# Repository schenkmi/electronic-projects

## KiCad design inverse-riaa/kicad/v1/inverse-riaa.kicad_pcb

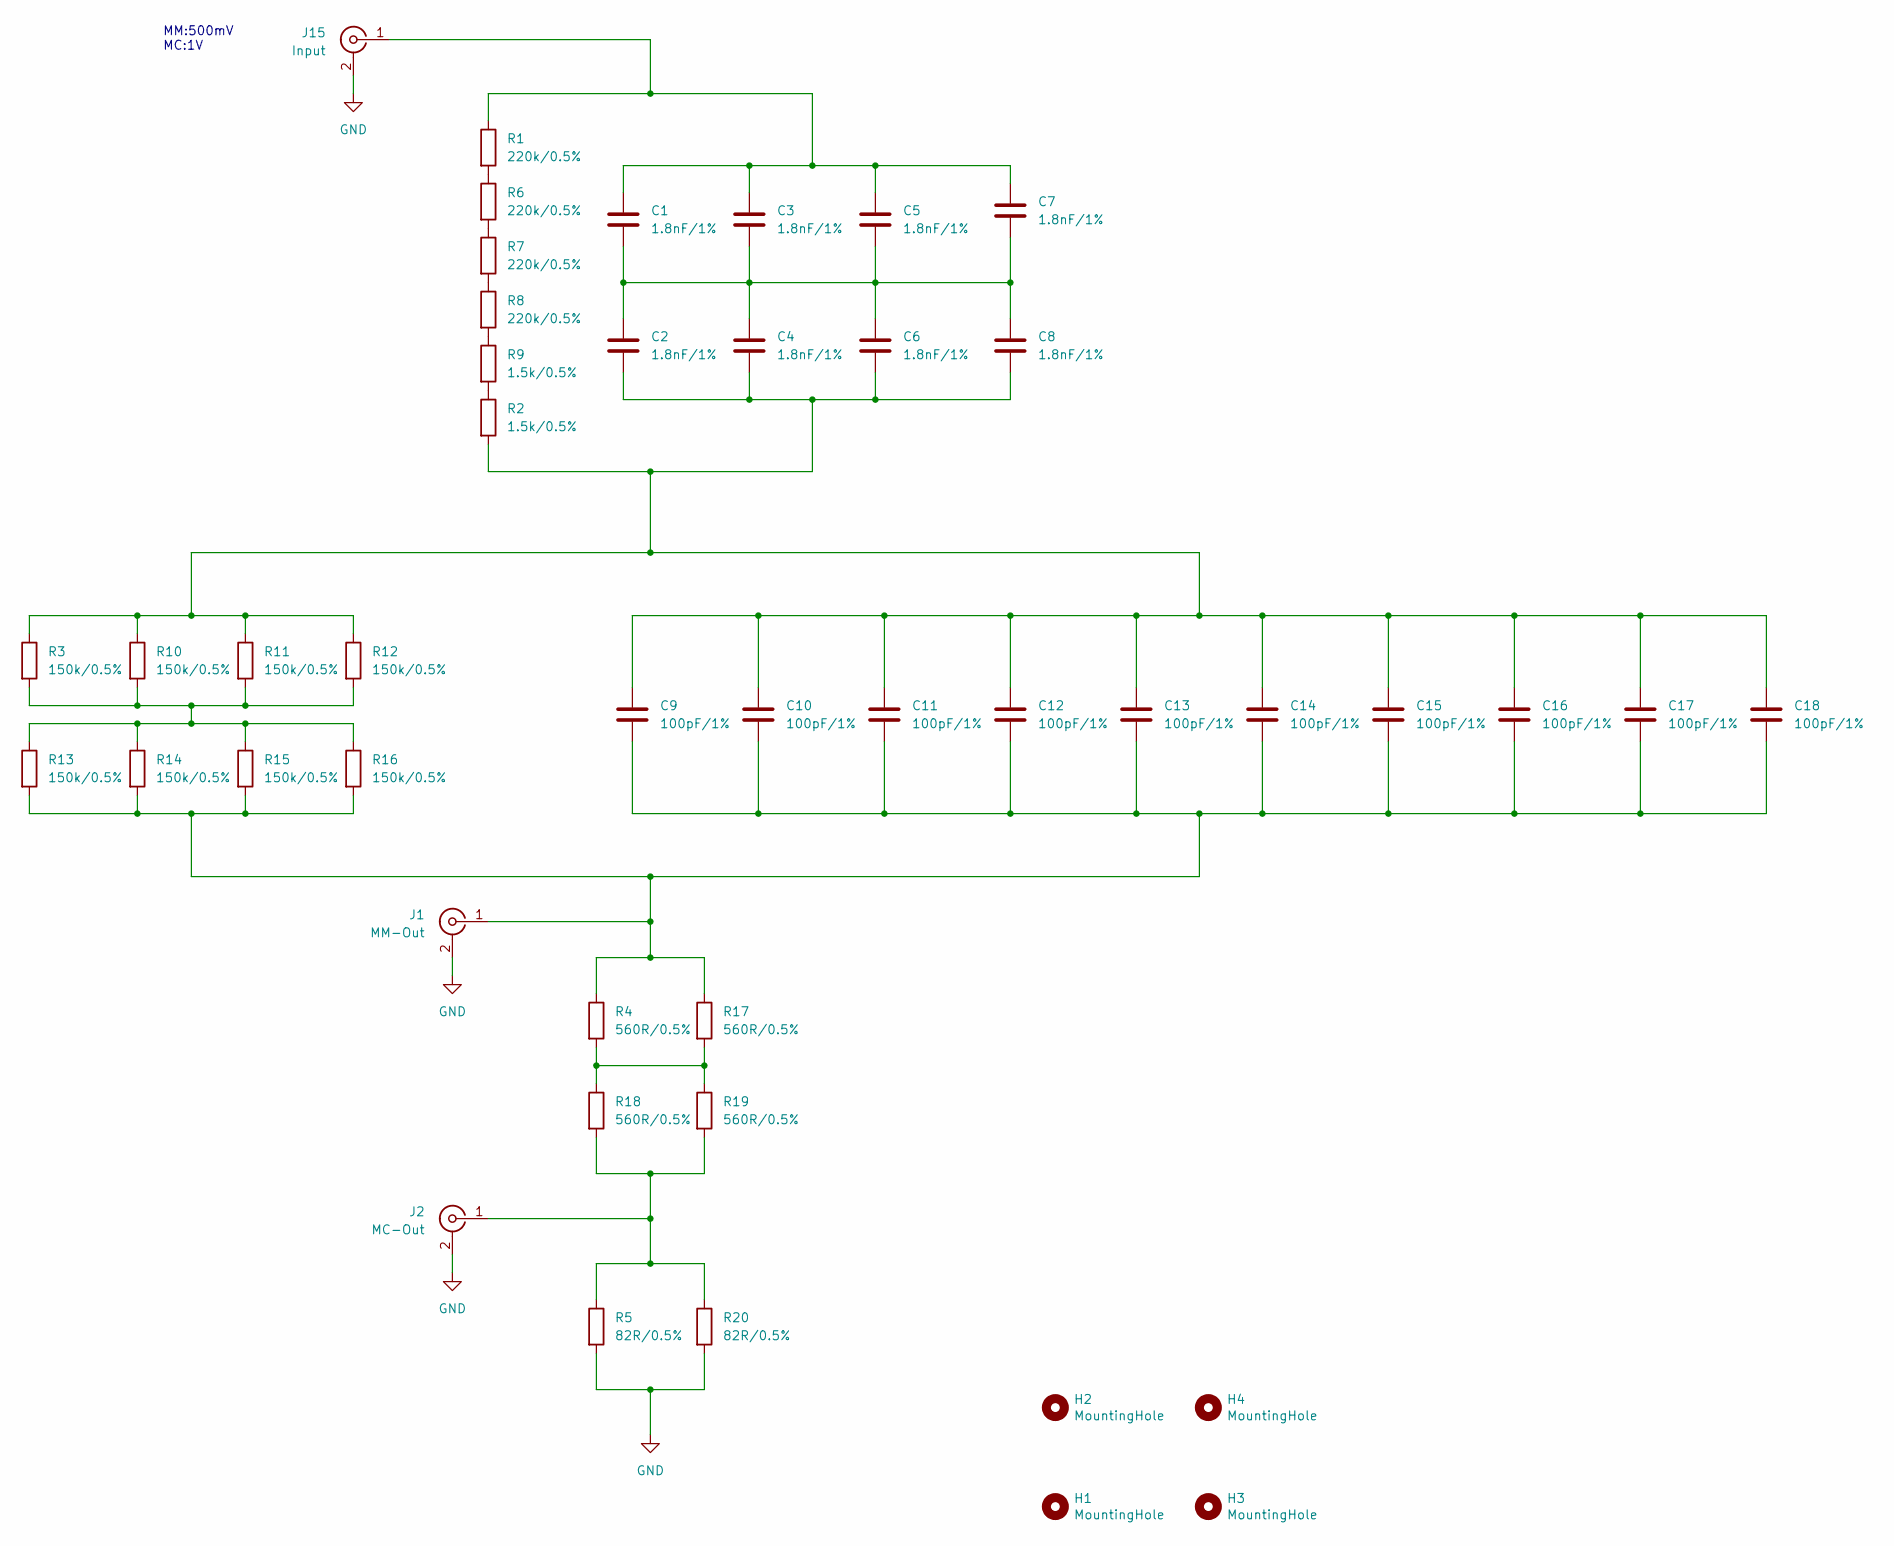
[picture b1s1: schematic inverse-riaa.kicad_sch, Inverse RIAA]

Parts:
C1, C2, C3, C4, C5, C6, C7, C8: 1.8nF/1%; C_0805_2012Metric_Pad1.18x1.45mm_HandSolder
C9, C10, C11, C12, C13, C14, C15, C16, C17, C18: 100pF/1%; C_0805_2012Metric_Pad1.18x1.45mm_HandSolder
H1, H2, H3, H4: MountingHole; MountingHole_3.2mm_M3_Pad_Via
J1: MM-Out; RCA-Phono_CUI-Devices_RCJ-02X_Vertical
J2: MC-Out; RCA-Phono_CUI-Devices_RCJ-02X_Vertical
J15: Input; RCA-Phono_CUI-Devices_RCJ-02X_Vertical
R1, R6, R7, R8: 220k/0.5%; R_0805_2012Metric_Pad1.20x1.40mm_HandSolder
R2, R9: 1.5k/0.5%; R_0805_2012Metric_Pad1.20x1.40mm_HandSolder
R3, R10, R11, R12, R13, R14, R15, R16: 150k/0.5%; R_0805_2012Metric_Pad1.20x1.40mm_HandSolder
R4, R17, R18, R19: 560R/0.5%; R_0805_2012Metric_Pad1.20x1.40mm_HandSolder
R5, R20: 82R/0.5%; R_0805_2012Metric_Pad1.20x1.40mm_HandSolder

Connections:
GND: J1.2 (Ext), J2.2 (Ext), J15.2 (Ext), R5.2, R20.2
unnamed: C1.2, C2.1, C3.2, C4.1, C5.2, C6.1, C7.2, C8.1
unnamed: C2.2, C4.2, C6.2, C8.2, C9.1, C10.1, C11.1, C12.1, C13.1, C14.1, C15.1, C16.1, C17.1, C18.1, R2.2, R3.1, R10.1, R11.1, R12.1
unnamed: C9.2, C10.2, C11.2, C12.2, C13.2, C14.2, C15.2, C16.2, C17.2, C18.2, J1.1 (In), R4.1, R13.2, R14.2, R15.2, R16.2, R17.1
unnamed: J2.1 (In), R5.1, R18.2, R19.2, R20.1
unnamed: C1.1, C3.1, C5.1, C7.1, J15.1 (In), R1.1
unnamed: R1.2, R6.1
unnamed: R2.1, R9.2
unnamed: R6.2, R7.1
unnamed: R7.2, R8.1
unnamed: R8.2, R9.1
unnamed: R3.2, R10.2, R11.2, R12.2, R13.1, R14.1, R15.1, R16.1
unnamed: R4.2, R17.2, R18.1, R19.1

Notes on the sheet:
MM:500mV MC:1V

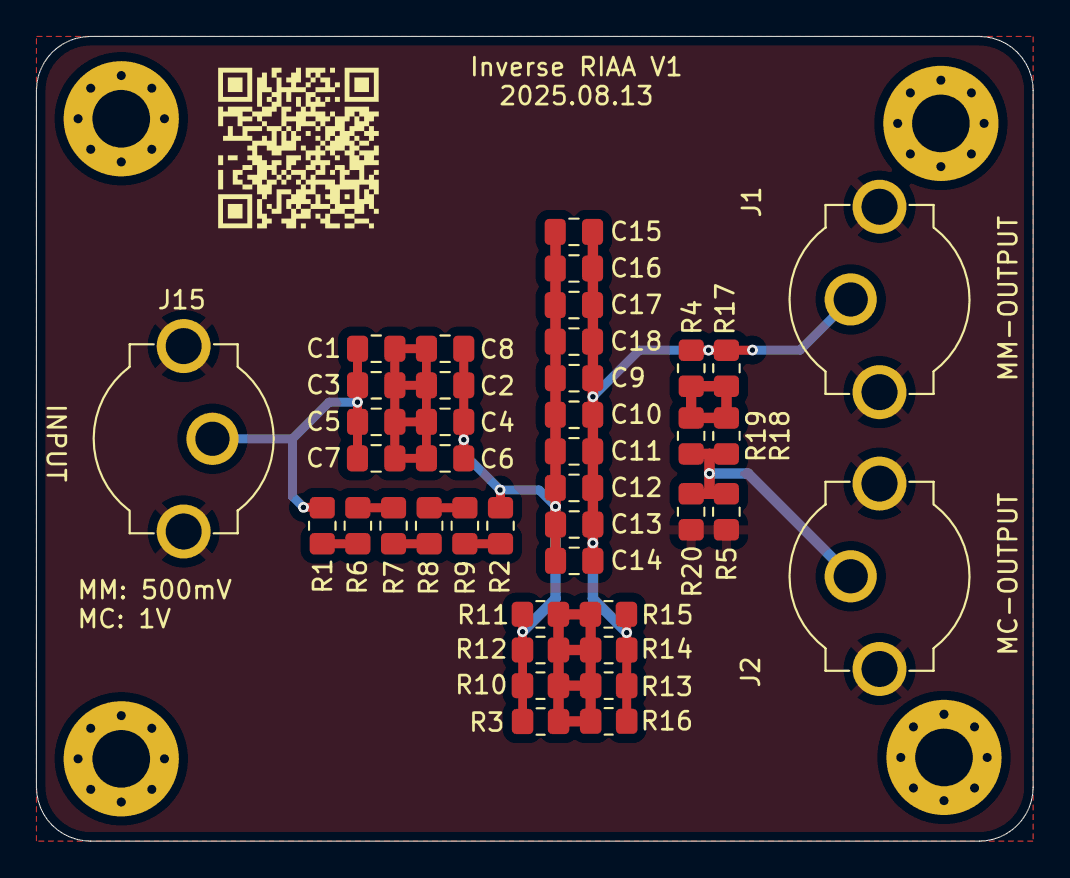
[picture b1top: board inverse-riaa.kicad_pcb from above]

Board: 2 copper layers, 55.4 x 44.7 mm, 45 parts (0 on the bottom side), 13 nets.

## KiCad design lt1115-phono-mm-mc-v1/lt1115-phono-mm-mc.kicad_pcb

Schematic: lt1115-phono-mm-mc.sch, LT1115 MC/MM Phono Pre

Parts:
C1: C; C_0805_2012Metric_Pad1.18x1.45mm_HandSolder
C2: 4.7uF; C_Rect_L7.2mm_W7.2mm_P5.00mm_FKS2_FKP2_MKS2_MKP2
C3: 2200uF/16V; CP_Radial_D10.0mm_P5.00mm
C4, C7, C11, C14: 220uF/25V; CP_Radial_D8.0mm_P3.50mm
C5, C6, C12, C13: 1uF; C_1210_3225Metric_Pad1.33x2.70mm_HandSolder
C8: 330pF; C_0805_2012Metric_Pad1.18x1.45mm_HandSolder
C9, C15: 3.9nF; C_1206_3216Metric_Pad1.33x1.80mm_HandSolder
C10: 15nF; C_1210_3225Metric_Pad1.33x2.70mm_HandSolder
C16, C19: 1uF; C_Rect_L7.2mm_W3.5mm_P5.00mm_FKS2_FKP2_MKS2_MKP2
C17, C18: 100nF; C_0805_2012Metric_Pad1.18x1.45mm_HandSolder
H1, H2, H3, H4: MountingHole; MountingHole_3.2mm_M3
HS1: Heatsink; Heatsink_Fischer_SK104-STC-STIC_35x13mm_2xDrill2.5mm
J1: INR; Pin_D1.0mm_L10.0mm
J2: INR_GND; Pin_D1.0mm_L10.0mm
J3: +15V; Pin_D1.0mm_L10.0mm
J4: GND; Pin_D1.0mm_L10.0mm
J5: -15V; Pin_D1.0mm_L10.0mm
J6: OUTR; Pin_D1.0mm_L10.0mm
J7: OUTR_GND; Pin_D1.0mm_L10.0mm
R1, R11: 100R; R_0805_2012Metric_Pad1.20x1.40mm_HandSolder
R2: 22.6R; R_0805_2012Metric_Pad1.20x1.40mm_HandSolder
R3: 210R; R_0805_2012Metric_Pad1.20x1.40mm_HandSolder
R4: 0R; R_0805_2012Metric_Pad1.20x1.40mm_HandSolder
R5: 449R; R_0805_2012Metric_Pad1.20x1.40mm_HandSolder
R6: 33.2k; R_0805_2012Metric_Pad1.20x1.40mm_HandSolder
R7: 17.8k; R_0805_2012Metric_Pad1.20x1.40mm_HandSolder
R8: 82.5k; R_0805_2012Metric_Pad1.20x1.40mm_HandSolder
R9: 33.2R; R_0805_2012Metric_Pad1.20x1.40mm_HandSolder
R10: 210k; R_0805_2012Metric_Pad1.20x1.40mm_HandSolder
R12: 49.9R; R_0805_2012Metric_Pad1.20x1.40mm_HandSolder
R13: 562R; R_0805_2012Metric_Pad1.20x1.40mm_HandSolder
R14: 25k; R_0805_2012Metric_Pad1.20x1.40mm_HandSolder
R15, R16: 100k; R_0805_2012Metric_Pad1.20x1.40mm_HandSolder
U1: LT1115; DIP-8_W7.62mm
U2: LM334M; SOIC-8_3.9x4.9mm_P1.27mm
U3: LT1010; TO-220-5_P3.4x3.7mm_StaggerOdd_Lead3.8mm_Vertical
U4: OPA188xxDBV; TSOT-23-5

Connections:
+15V: C4.1, C5.1, C11.1, C12.1, C17.1, J3.1, R12.1, U1.7 (V+), U3.2 (V+), U4.5 (V+)
-15V: C6.2, C7.2, C13.2, C14.2, C18.2, J5.1, R9.2, U1.4 (V-), U2.2, U2.3, U2.6, U2.7, U3.3 (V-), U4.2 (V-)
GND: C1.2, C2.1, C3.2, C4.2, C5.2, C6.1, C7.1, C11.2, C12.2, C13.1, C14.1, C15.2, C17.2, C18.1, C19.1, J2.1, J4.1, J7.1, R1.2, R6.1, R14.2, R15.2
unnamed: C1.1, J1.1, R1.1, U1.3 (+)
unnamed: C2.2, C3.1, R3.2, R4.2, R8.2
unnamed: C8.2, C9.2, R5.1, R7.2
unnamed: C8.1, C9.1, C10.2, R7.1, R10.2
unnamed: C15.1, J6.1, R13.1, R14.1
unnamed: C16.2, R16.1, U4.4 (-)
unnamed: C19.2, R15.1, U4.3 (+)
unnamed: R2.1, R5.2, U1.2 (-)
unnamed: R2.2, R3.1, R4.1
unnamed: R6.2, U1.1 (TRIM)
unnamed: R9.1, U2.1
unnamed: R11.1, U3.1 (IN)
unnamed: R11.2, U1.6, U2.4
unnamed: R12.2, U3.4 (BIAS)
SERVO_INR: C10.1, R8.1, R10.1, R13.2, R16.2, U3.5 (OUT)
SERVO_OUTR: C16.1, U1.8 (TRIM), U4.1

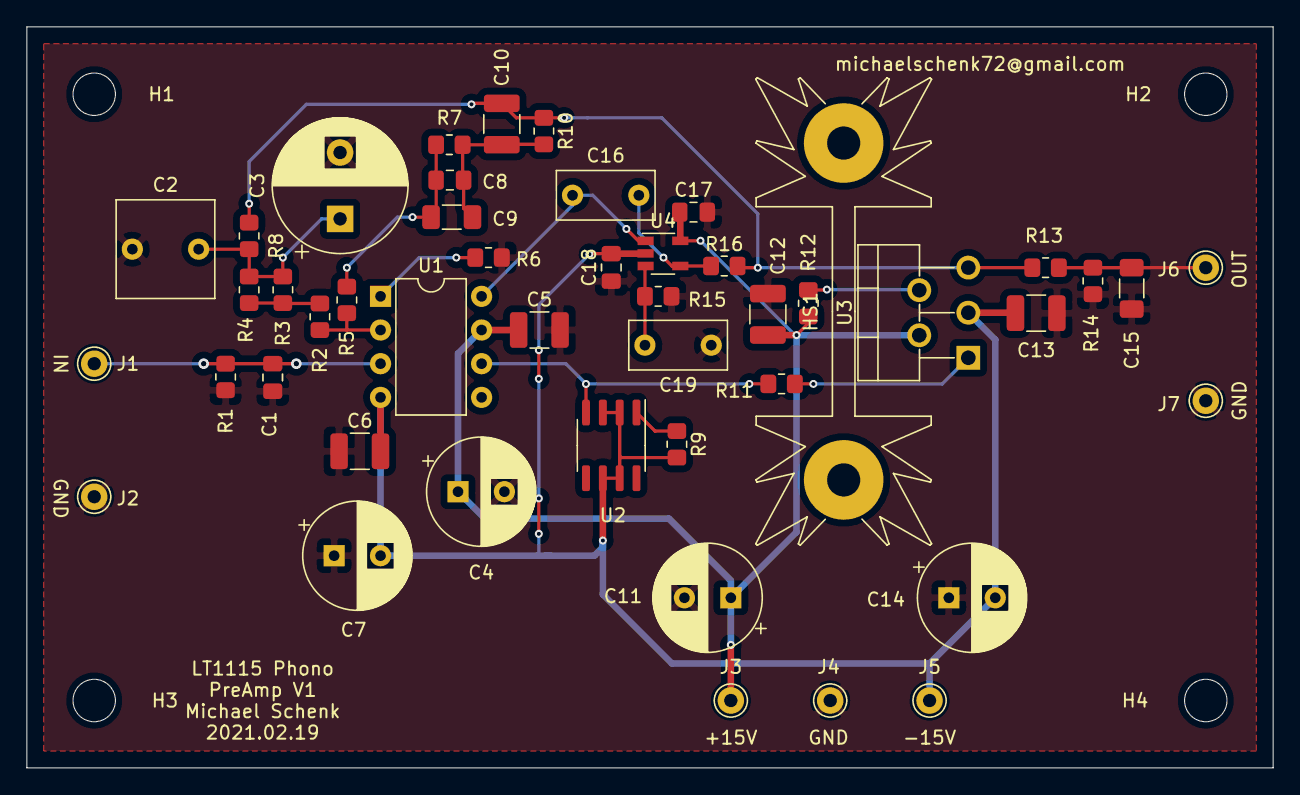
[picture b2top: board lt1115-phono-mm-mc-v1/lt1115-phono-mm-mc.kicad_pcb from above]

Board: 2 copper layers, 94.0 x 55.9 mm, 51 parts (0 on the bottom side), 19 nets.

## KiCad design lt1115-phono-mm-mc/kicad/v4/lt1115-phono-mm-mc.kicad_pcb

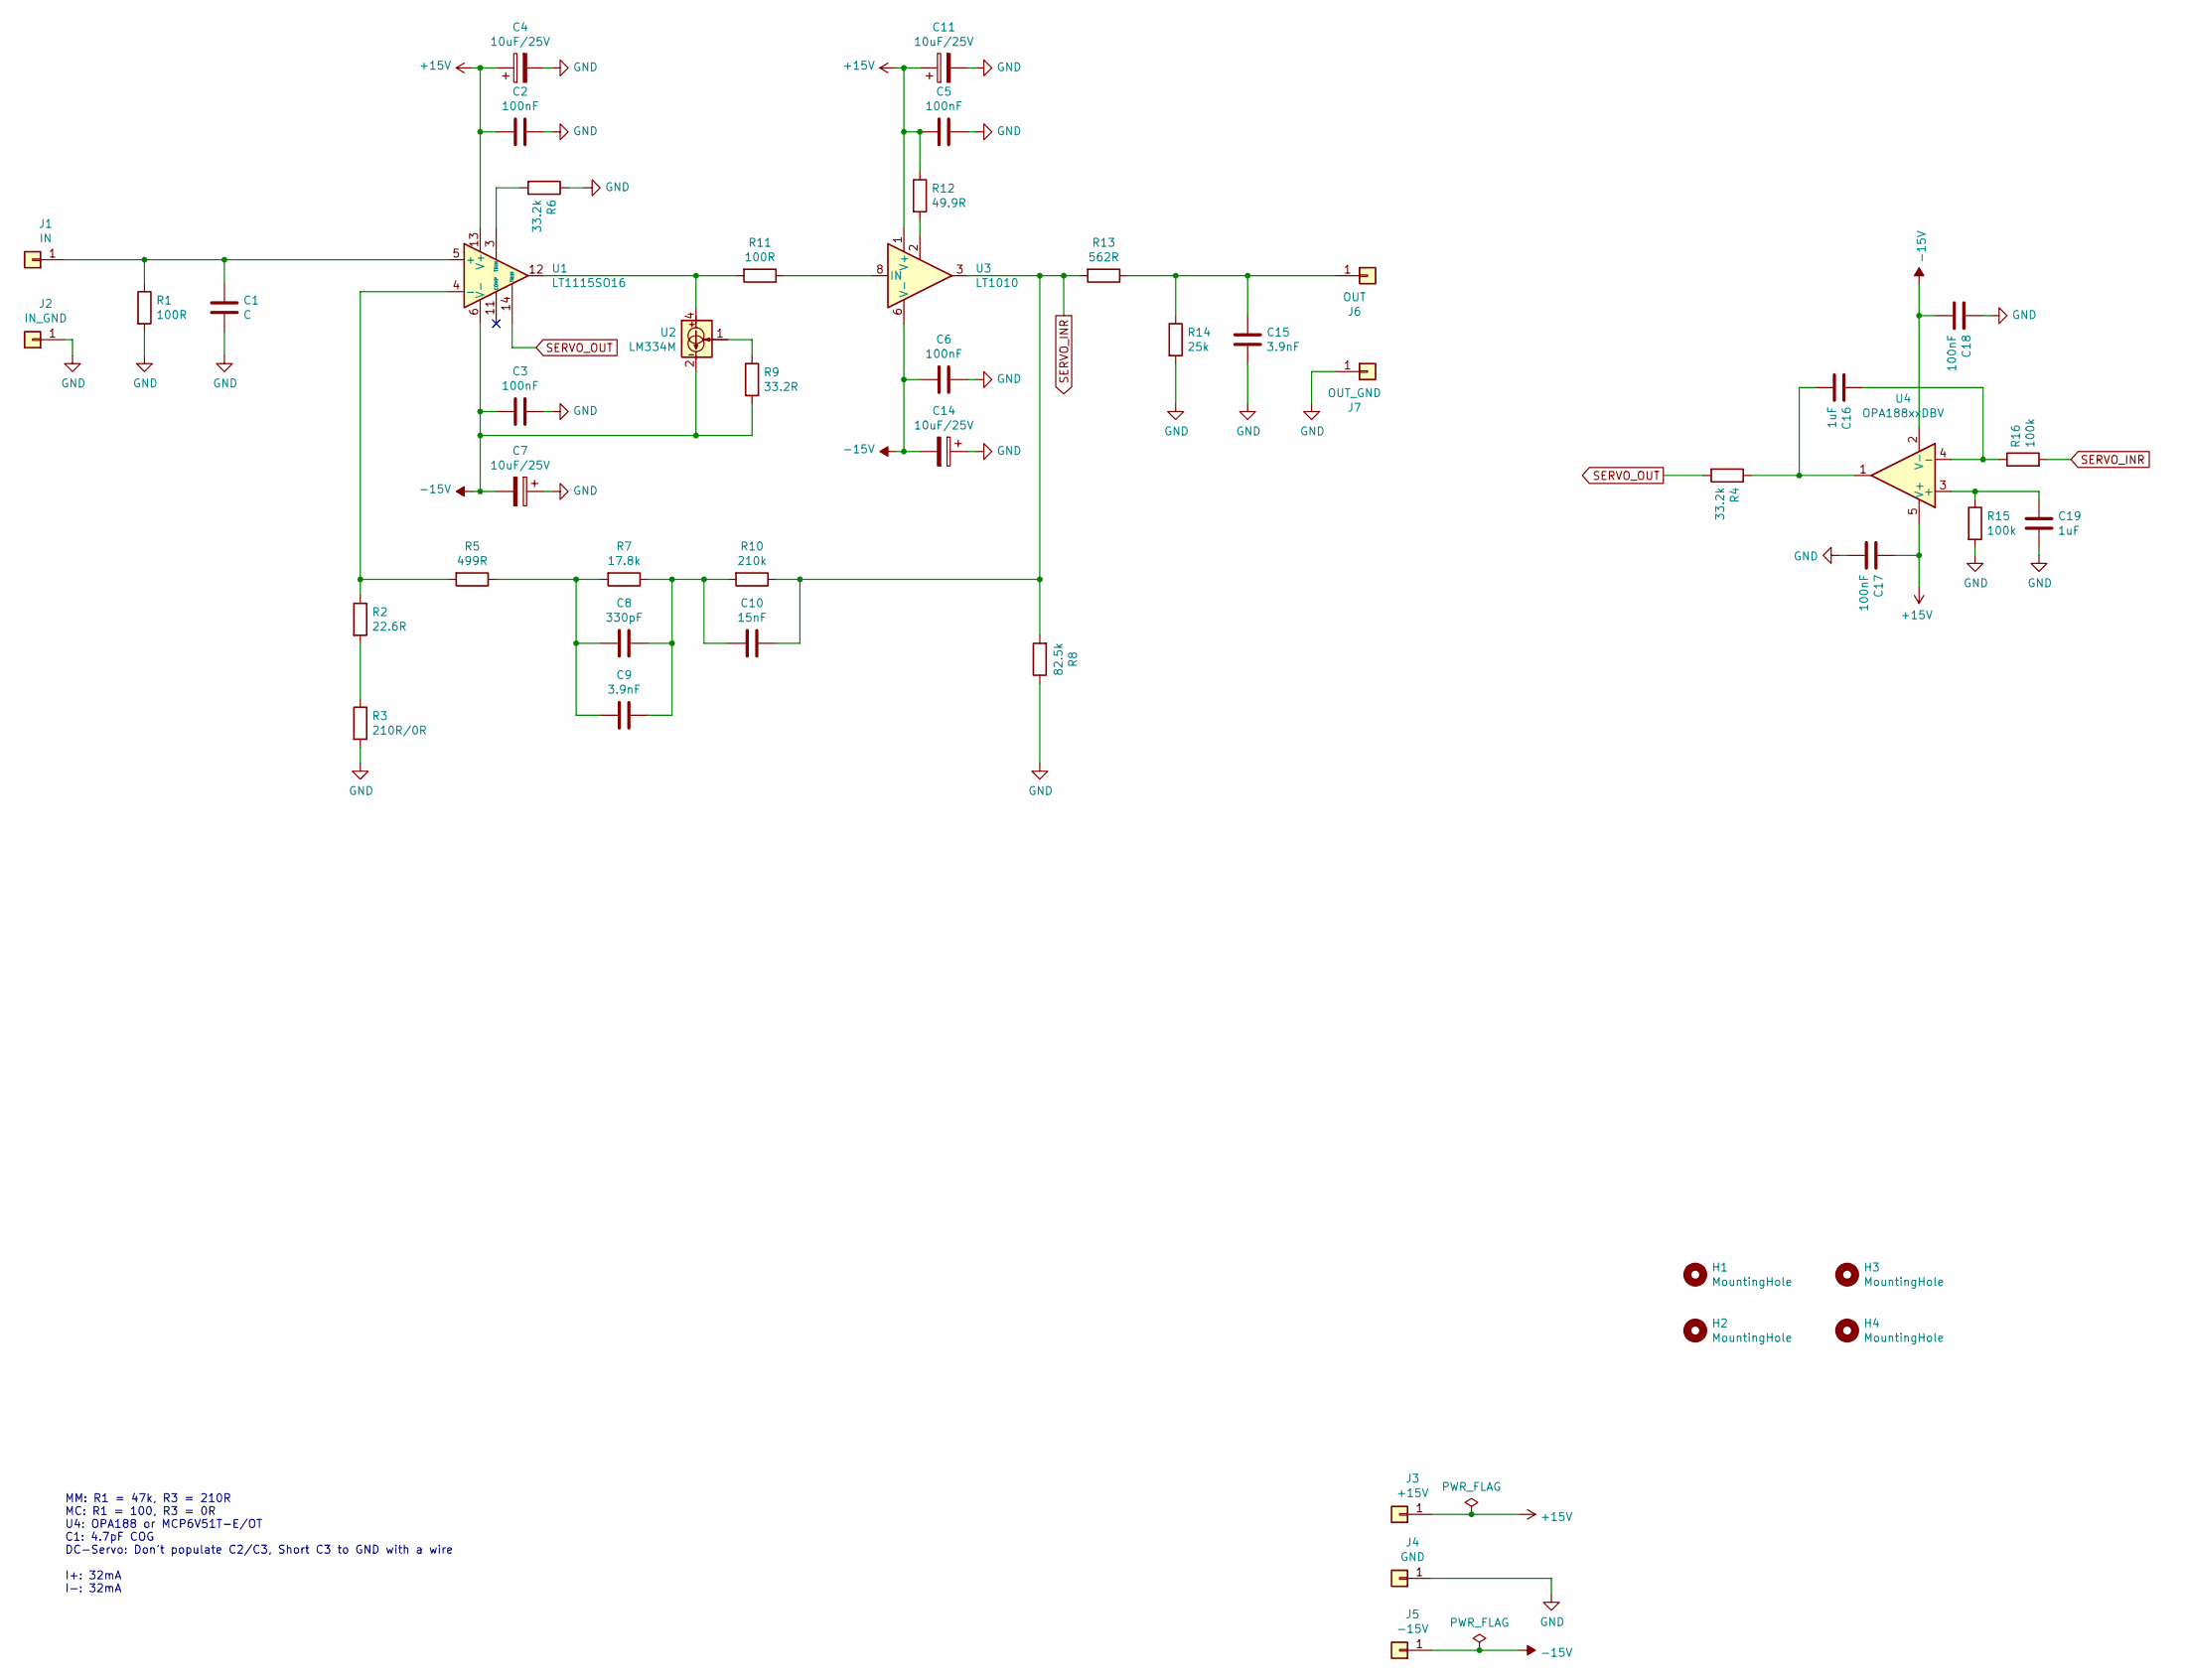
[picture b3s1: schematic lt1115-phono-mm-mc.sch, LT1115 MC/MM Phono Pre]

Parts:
C1: C; C_0805_2012Metric_Pad1.18x1.45mm_HandSolder
C2, C3, C5, C6: 100nF; C_1210_3225Metric_Pad1.33x2.70mm_HandSolder
C4, C7, C11, C14: 10uF/25V; CP_Elec_6.3x5.8
C8: 330pF; C_0805_2012Metric_Pad1.18x1.45mm_HandSolder
C9, C15: 3.9nF; C_1206_3216Metric_Pad1.33x1.80mm_HandSolder
C10: 15nF; C_1210_3225Metric_Pad1.33x2.70mm_HandSolder
C16, C19: 1uF; C_1210_3225Metric_Pad1.33x2.70mm_HandSolder
C17, C18: 100nF; C_0805_2012Metric_Pad1.18x1.45mm_HandSolder
H1, H2, H3, H4: MountingHole; MountingHole_3.2mm_M3
J1: IN; Pin_D1.0mm_L10.0mm
J2: IN_GND; Pin_D1.0mm_L10.0mm
J3: +15V; Pin_D1.0mm_L10.0mm
J4: GND; Pin_D1.0mm_L10.0mm
J5: -15V; Pin_D1.0mm_L10.0mm
J6: OUT; Pin_D1.0mm_L10.0mm
J7: OUT_GND; Pin_D1.0mm_L10.0mm
R1, R11: 100R; R_0805_2012Metric_Pad1.20x1.40mm_HandSolder
R2: 22.6R; R_0805_2012Metric_Pad1.20x1.40mm_HandSolder
R3: 210R/0R; R_0805_2012Metric_Pad1.20x1.40mm_HandSolder
R4, R6: 33.2k; R_0805_2012Metric_Pad1.20x1.40mm_HandSolder
R5: 499R; R_0805_2012Metric_Pad1.20x1.40mm_HandSolder
R7: 17.8k; R_0805_2012Metric_Pad1.20x1.40mm_HandSolder
R8: 82.5k; R_0805_2012Metric_Pad1.20x1.40mm_HandSolder
R9: 33.2R; R_0805_2012Metric_Pad1.20x1.40mm_HandSolder
R10: 210k; R_0805_2012Metric_Pad1.20x1.40mm_HandSolder
R12: 49.9R; R_0805_2012Metric_Pad1.20x1.40mm_HandSolder
R13: 562R; R_0805_2012Metric_Pad1.20x1.40mm_HandSolder
R14: 25k; R_0805_2012Metric_Pad1.20x1.40mm_HandSolder
R15, R16: 100k; R_0805_2012Metric_Pad1.20x1.40mm_HandSolder
U1: LT1115SO16; SOIC-16W_7.5x10.3mm_P1.27mm
U2: LM334M; SOIC-8_3.9x4.9mm_P1.27mm
U3: LT1010; DFN-8-1EP_3x3mm_P0.5mm_EP1.66x2.38mm
U4: OPA188xxDBV; TSOT-23-5

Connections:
+15V: C2.2, C4.1, C5.2, C11.1, C17.1, J3.1, R12.1, U1.13 (V+), U3.1 (V+), U4.5 (V+)
-15V: C3.2, C6.2, C7.2, C14.2, C18.2, J5.1, R9.2, U1.6 (V-), U2.2, U2.3, U2.6, U2.7, U3.6 (V-), U4.2 (V-)
GND: C1.2, C2.1, C3.1, C4.2, C5.1, C6.1, C7.1, C11.2, C14.1, C15.2, C17.2, C18.1, C19.1, J2.1, J4.1, J7.1, R1.2, R3.2, R6.1, R8.1, R14.2, R15.2
unnamed: C1.1, J1.1, R1.1, U1.5 (+)
unnamed: C8.2, C9.2, R5.1, R7.2
unnamed: C8.1, C9.1, C10.2, R7.1, R10.2
unnamed: C15.1, J6.1, R13.1, R14.1
unnamed: C16.1, R4.1, U4.1
unnamed: C16.2, R16.1, U4.4 (-)
unnamed: C19.2, R15.1, U4.3 (+)
unnamed: R2.1, R5.2, U1.4 (-)
unnamed: R2.2, R3.1
unnamed: R6.2, U1.3 (TRIM)
unnamed: R9.1, U2.1
unnamed: R11.1, U3.8 (IN)
unnamed: R11.2, U1.12, U2.4
unnamed: R12.2, U3.2
SERVO_INR: C10.1, R8.2, R10.1, R13.2, R16.2, U3.3
SERVO_OUT: R4.2, U1.14 (TRIM)

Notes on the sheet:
MM: R1 = 47k, R3 = 210R MC: R1 = 100, R3 = 0R U4: OPA188 or MCP6V51T-E/OT C1: 4.7pF COG DC-Servo: Don’t populate C2/C3, Short C3 to GND with a wire I+: 32mA I-: 32mA

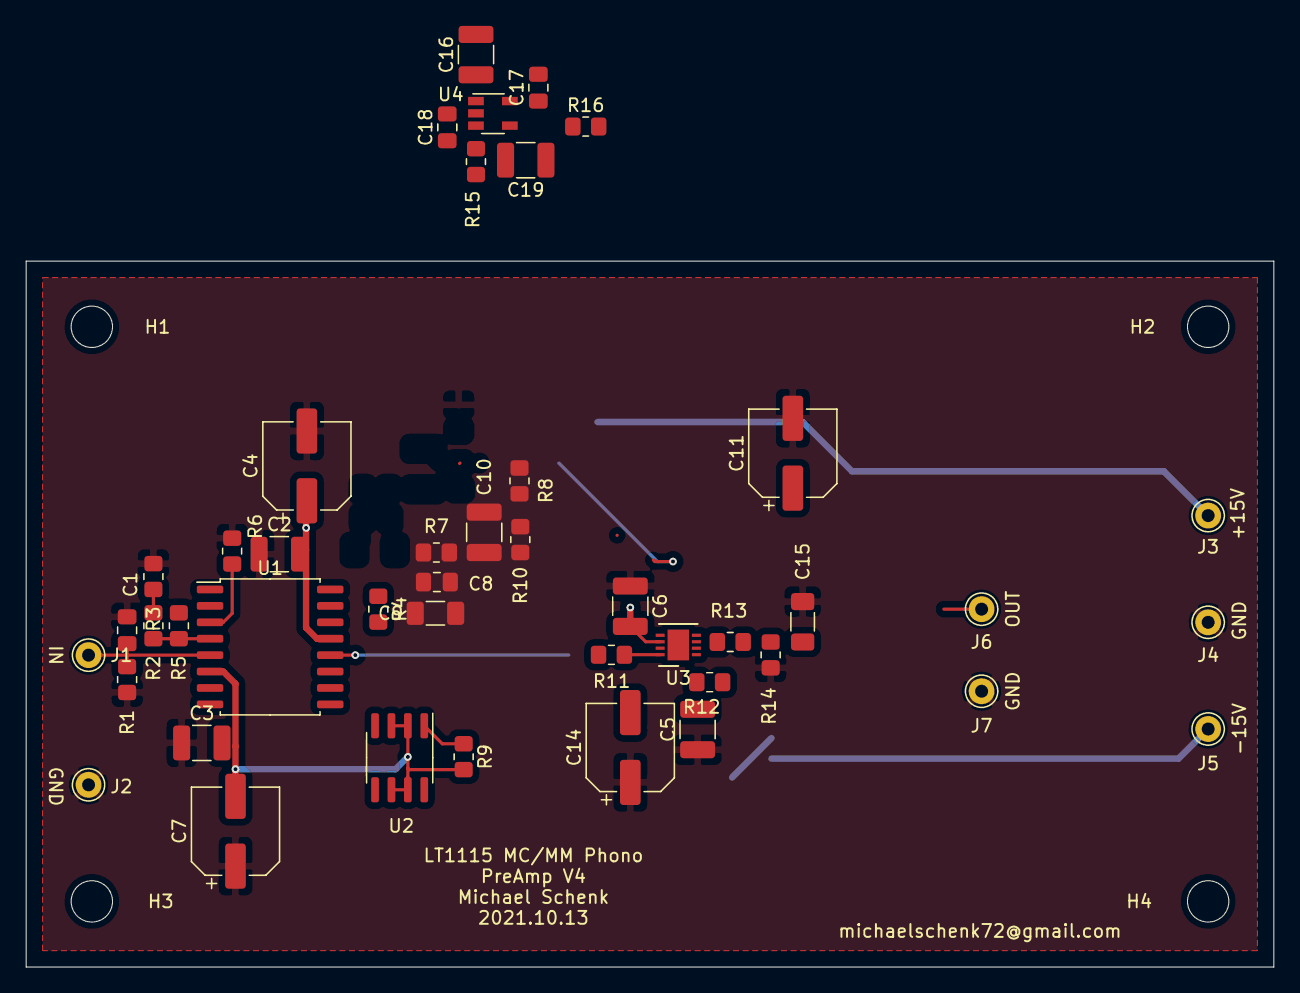
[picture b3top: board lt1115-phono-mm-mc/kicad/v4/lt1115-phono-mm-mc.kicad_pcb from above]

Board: 2 copper layers, 96.5 x 54.6 mm, 48 parts (0 on the bottom side), 19 nets.

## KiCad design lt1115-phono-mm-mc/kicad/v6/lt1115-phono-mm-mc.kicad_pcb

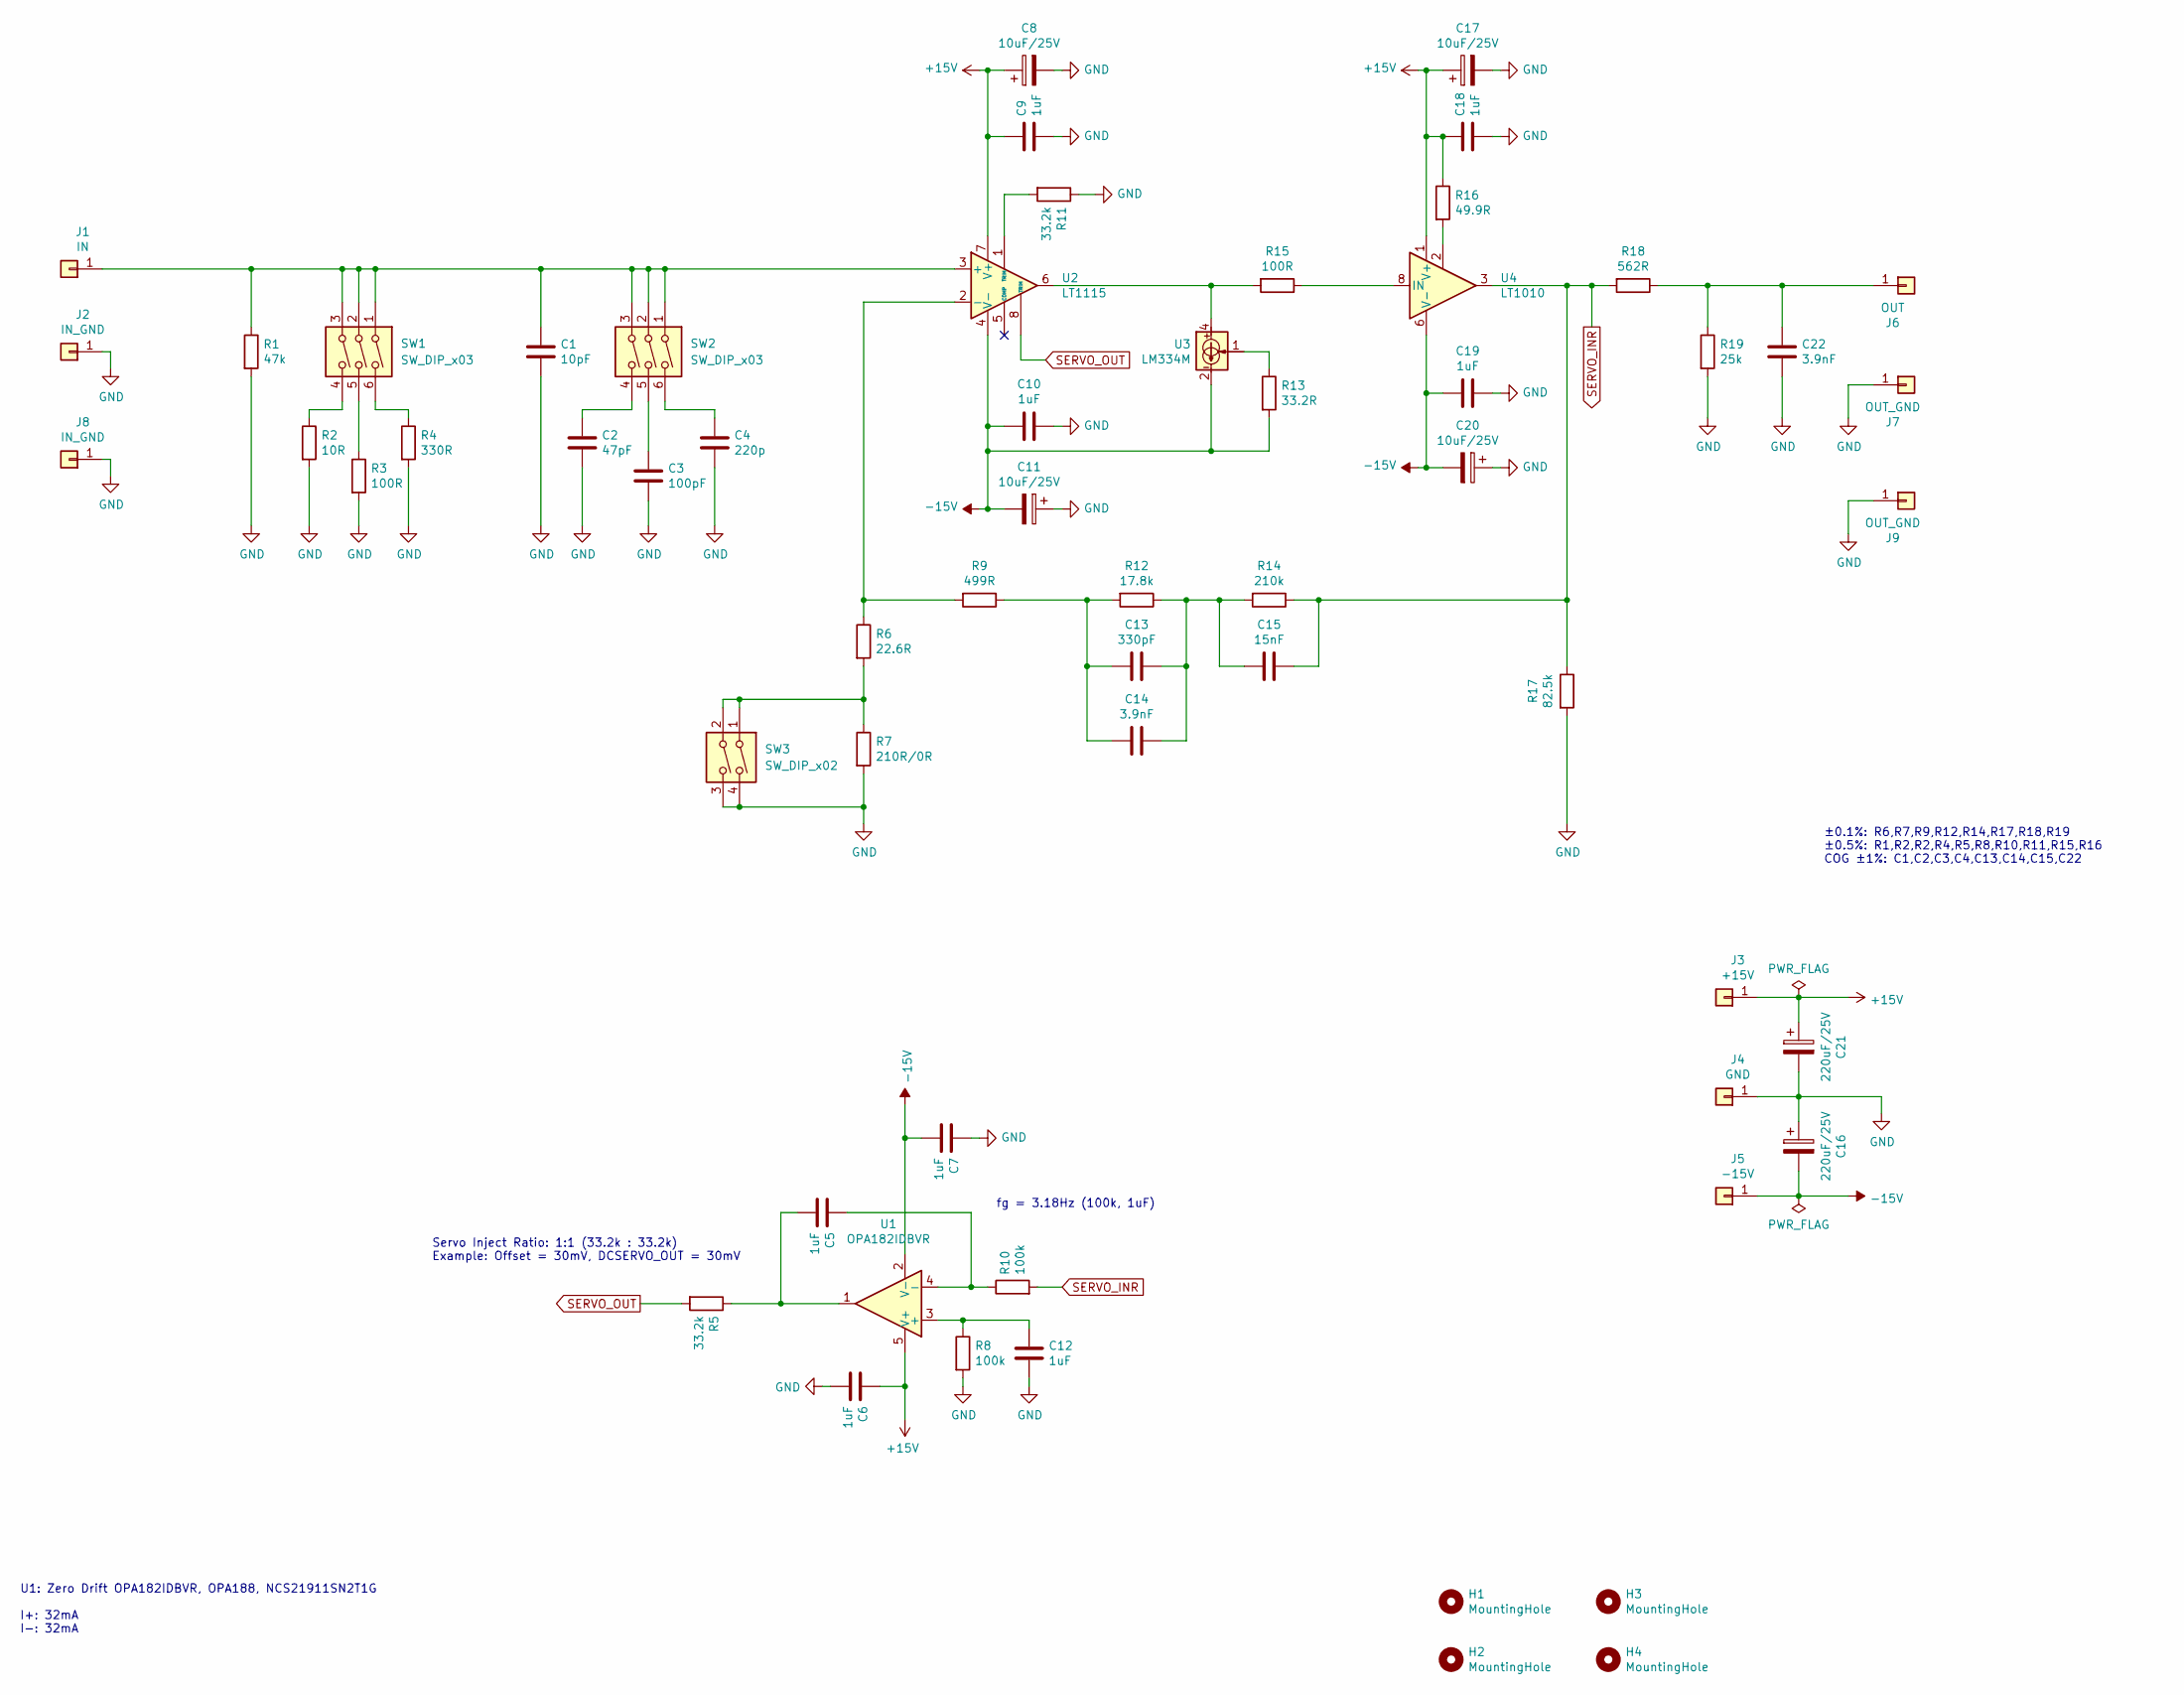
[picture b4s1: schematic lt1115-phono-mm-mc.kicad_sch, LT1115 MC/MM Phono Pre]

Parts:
C1: 10pF; C_0603_1608Metric_Pad1.08x0.95mm_HandSolder
C2: 47pF; C_0603_1608Metric_Pad1.08x0.95mm_HandSolder
C3: 100pF; C_0603_1608Metric_Pad1.08x0.95mm_HandSolder
C4: 220p; C_0603_1608Metric_Pad1.08x0.95mm_HandSolder
C5, C12: 1uF; C_Rect_L7.2mm_W3.5mm_P5.00mm_FKS2_FKP2_MKS2_MKP2
C6, C7, C9, C10, C18, C19: 1uF; C_0805_2012Metric_Pad1.18x1.45mm_HandSolder
C8, C11, C17, C20: 10uF/25V; CP_EIA-3528-12_Kemet-T_HandSolder
C13: 330pF; C_0603_1608Metric_Pad1.08x0.95mm_HandSolder
C14, C22: 3.9nF; C_0603_1608Metric_Pad1.08x0.95mm_HandSolder
C15: 15nF; C_0603_1608Metric_Pad1.08x0.95mm_HandSolder
C16, C21: 220uF/25V; CP_Radial_D8.0mm_P3.50mm
H1, H2, H3, H4: MountingHole; MountingHole_3.2mm_M3_Pad_Via
J1: IN; Pin_D1.0mm_L10.0mm
J2, J8: IN_GND; Pin_D1.0mm_L10.0mm
J3: +15V; Pin_D1.0mm_L10.0mm
J4: GND; Pin_D1.0mm_L10.0mm
J5: -15V; Pin_D1.0mm_L10.0mm
J6: OUT; Pin_D1.0mm_L10.0mm
J7, J9: OUT_GND; Pin_D1.0mm_L10.0mm
R1: 47k; R_0805_2012Metric_Pad1.20x1.40mm_HandSolder
R2: 10R; R_0805_2012Metric_Pad1.20x1.40mm_HandSolder
R3, R15: 100R; R_0805_2012Metric_Pad1.20x1.40mm_HandSolder
R4: 330R; R_0805_2012Metric_Pad1.20x1.40mm_HandSolder
R5, R11: 33.2k; R_0805_2012Metric_Pad1.20x1.40mm_HandSolder
R6: 22.6R; R_0805_2012Metric_Pad1.20x1.40mm_HandSolder
R7: 210R/0R; R_0805_2012Metric_Pad1.20x1.40mm_HandSolder
R8, R10: 100k; R_0805_2012Metric_Pad1.20x1.40mm_HandSolder
R9: 499R; R_0805_2012Metric_Pad1.20x1.40mm_HandSolder
R12: 17.8k; R_0805_2012Metric_Pad1.20x1.40mm_HandSolder
R13: 33.2R; R_0805_2012Metric_Pad1.20x1.40mm_HandSolder
R14: 210k; R_0805_2012Metric_Pad1.20x1.40mm_HandSolder
R16: 49.9R; R_0805_2012Metric_Pad1.20x1.40mm_HandSolder
R17: 82.5k; R_0805_2012Metric_Pad1.20x1.40mm_HandSolder
R18: 562R; R_0805_2012Metric_Pad1.20x1.40mm_HandSolder
R19: 25k; R_0805_2012Metric_Pad1.20x1.40mm_HandSolder
SW1, SW2: SW_DIP_x03; SW_DIP_SPSTx03_Slide_6.7x9.18mm_W8.61mm_P2.54mm_LowProfile
SW3: SW_DIP_x02; SW_DIP_SPSTx02_Slide_6.7x6.64mm_W8.61mm_P2.54mm_LowProfile
U1: OPA182IDBVR; TSOT-23-5
U2: LT1115; DIP-8_W7.62mm_Socket
U3: LM334M; SOIC-8_3.9x4.9mm_P1.27mm
U4: LT1010; DIP-8_W7.62mm_Socket

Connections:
+15V: C6.1, C8.1, C9.1, C17.1, C18.1, C21.1, J3.1, R16.1, U1.5 (V+), U2.7 (V+), U4.1 (V+)
-15V: C7.2, C10.2, C11.2, C16.2, C19.2, C20.2, J5.1, R13.2, U1.2 (V-), U2.4 (V-), U3.2, U3.3, U3.6, U3.7, U4.6 (V-)
GND: C1.2, C2.2, C3.2, C4.2, C6.2, C7.1, C8.2, C9.2, C10.1, C11.1, C12.1, C16.1, C17.2, C18.2, C19.1, C20.1, C21.2, C22.2, J2.1, J4.1, J7.1, J8.1, J9.1, R1.2, R2.2, R3.2, R4.2, R7.2, R8.2, R11.1, R17.2, R19.2, SW3.3, SW3.4
unnamed: C2.1, SW2.4
unnamed: C3.1, SW2.5
unnamed: C4.1, SW2.6
unnamed: C5.1, R5.1, U1.1
unnamed: C13.1, C14.1, C15.2, R12.1, R14.2
unnamed: C13.2, C14.2, R9.1, R12.2
unnamed: C1.1, J1.1, R1.1, SW1.1, SW1.2, SW1.3, SW2.1, SW2.2, SW2.3, U2.3 (+)
unnamed: C22.1, J6.1, R18.1, R19.1
unnamed: R2.1, SW1.4
unnamed: R3.1, SW1.5
unnamed: R4.1, SW1.6
unnamed: R6.2, R7.1, SW3.1, SW3.2
unnamed: R11.2, U2.1 (TRIM)
unnamed: R13.1, U3.1
unnamed: R15.2, U2.6, U3.4
unnamed: R16.2, U4.2
unnamed: C12.2, R8.1, U1.3 (+)
unnamed: C5.2, R10.1, U1.4 (-)
unnamed: R6.1, R9.2, U2.2 (-)
unnamed: R15.1, U4.8 (IN)
SERVO_INR: C15.1, R10.2, R14.1, R17.1, R18.2, U4.3
SERVO_OUT: R5.2, U2.8 (TRIM)

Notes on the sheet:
Servo Inject Ratio: 1:1 (33.2k : 33.2k) Example: Offset = 30mV, DCSERVO_OUT = 30mV
U1: Zero Drift OPA182IDBVR, OPA188, NCS21911SN2T1G I+: 32mA I-: 32mA
±0.1%: R6,R7,R9,R12,R14,R17,R18,R19 ±0.5%: R1,R2,R2,R4,R5,R8,R10,R11,R15,R16 COG ±1%: C1,C2,C3,C4,C13,C14,C15,C22
fg = 3.18Hz (100k, 1uF)

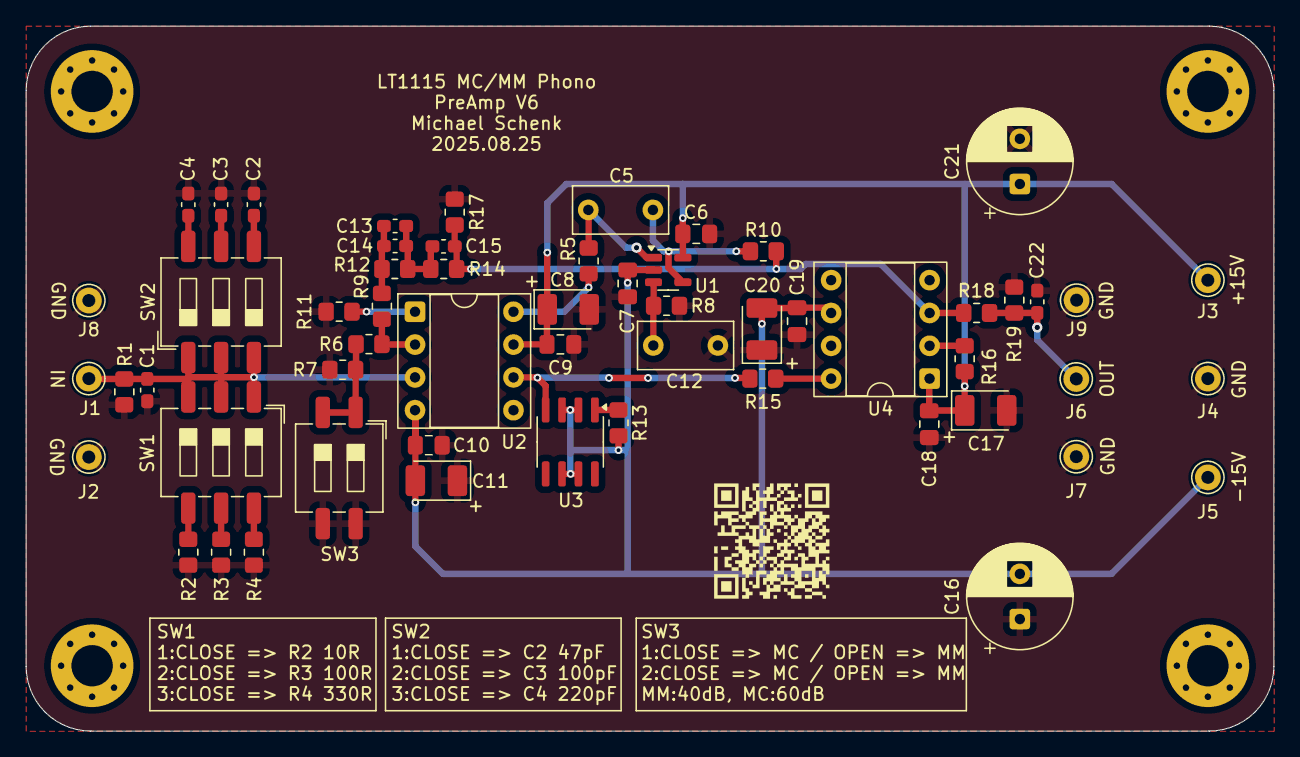
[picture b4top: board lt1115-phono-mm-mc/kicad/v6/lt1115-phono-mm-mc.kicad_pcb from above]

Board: 2 copper layers, 96.6 x 54.6 mm, 61 parts (0 on the bottom side), 25 nets.
